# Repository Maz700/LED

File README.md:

# LED
My first project is the LED Chaser board. Since I am a complete beginner, my first project is a small and simple project just to learn the basics of PCB design and learn soldering. I am following the Blinky guide for this project. I am making the PCB in the shape of an my team's oar blade because I like rowing.

| Reference | Item              | Description                     | Quantity | Unit Price (USD) | Total (USD) | Link                                                                                                                           |
|----------|-------------------|---------------------------------|----------|------------------|-------------|--------------------------------------------------------------------------------------------------------------------------------|
| C1       | Capacitor         | CAP ALUM 1UF 20% 50V RADIAL TH  | 1        | $0.10            | $0.10       | https://www.digikey.com/en/products/detail/w%C3%BCrth-elektronik/860020672005/5727088                                          |
| C2       | Capacitor         | CER CAP 0.01UF 50V              | 1        | $0.24            | $0.24       | https://www.digikey.com/en/products/detail/kemet/C410C103Z5U5TA7200/12701821                                                   |
| D1-10    | LED               | LED COOL WHITE 5MM ROUND T/H    | 10       | $0.22            | $2.23       | https://www.digikey.com/en/products/detail/cree-led/C543A-WMN-CCCKK141/9959490                                                 |
| R1       | Resistor          | RES 1K OHM 1% 1/4W AXIAL        | 1        | $0.10            | $0.10       | https://www.digikey.com/en/products/detail/yageo/MFR-25FRF52-1K/14891                                                          |
| R2       | Resistor          | RES 470 OHM 1% 1/4W AXIAL       | 1        | $0.10            | $0.10       | https://www.digikey.com/en/products/detail/yageo/MFR-25FBF52-470R/9138172?s=N4IgTCBcDaILIDEBKBaMBWBAhB6woBYB2ABlQDkAREAXQF8g   |
| RV1      | Variable Resistor | TRIMMER 50K OHM 0.5W PC PIN TOP | 1        | $2.20            | $2.20       | https://www.digikey.com/en/products/detail/bourns-inc/3386P-1-503TLF/1232551?s=N4IgTCBcDaIMxwBwDYAKBaArABjgFQBkAxdAOQBEQBdAXyA |
| TP1      | Test Point        | PC TEST POINT SLOTTED           | 1        | $0.15            | $0.15       | https://www.digikey.com/en/products/detail/keystone-electronics/1035/315151                                                    |
| TP2      | Test Point        | PC TEST POINT SLOTTED           | 1        | $0.15            | $0.15       | https://www.digikey.com/en/products/detail/keystone-electronics/1035/315151                                                    |
| TP3      | Test Point        | PC TEST POINT SLOTTED           | 1        | $0.15            | $0.15       | https://www.digikey.com/en/products/detail/keystone-electronics/1035/315151                                                    |
| U1       | NE555PS           | IC OSC TIMER SINGLE 100KHZ 8SO  | 1        | $1.10            | $1.10       | https://www.digikey.com/en/products/detail/texas-instruments/NE555PS/9692573?s=N4IgTCBcDa4JwDYC0A5AogViwBQMqoBEQBdAXyA         |
| U2       | CD4017BE          | IC DECADE COUNTER 10BIT 16DIP   | 1        | $1.27            | $1.27       | https://www.digikey.com/en/products/detail/texas-instruments/CD4017BE/67253      
| PCB      | PCB               | PCB                             | 1        | $2               | $2          | https://cart.jlcpcb.com/quote                                                                                               |

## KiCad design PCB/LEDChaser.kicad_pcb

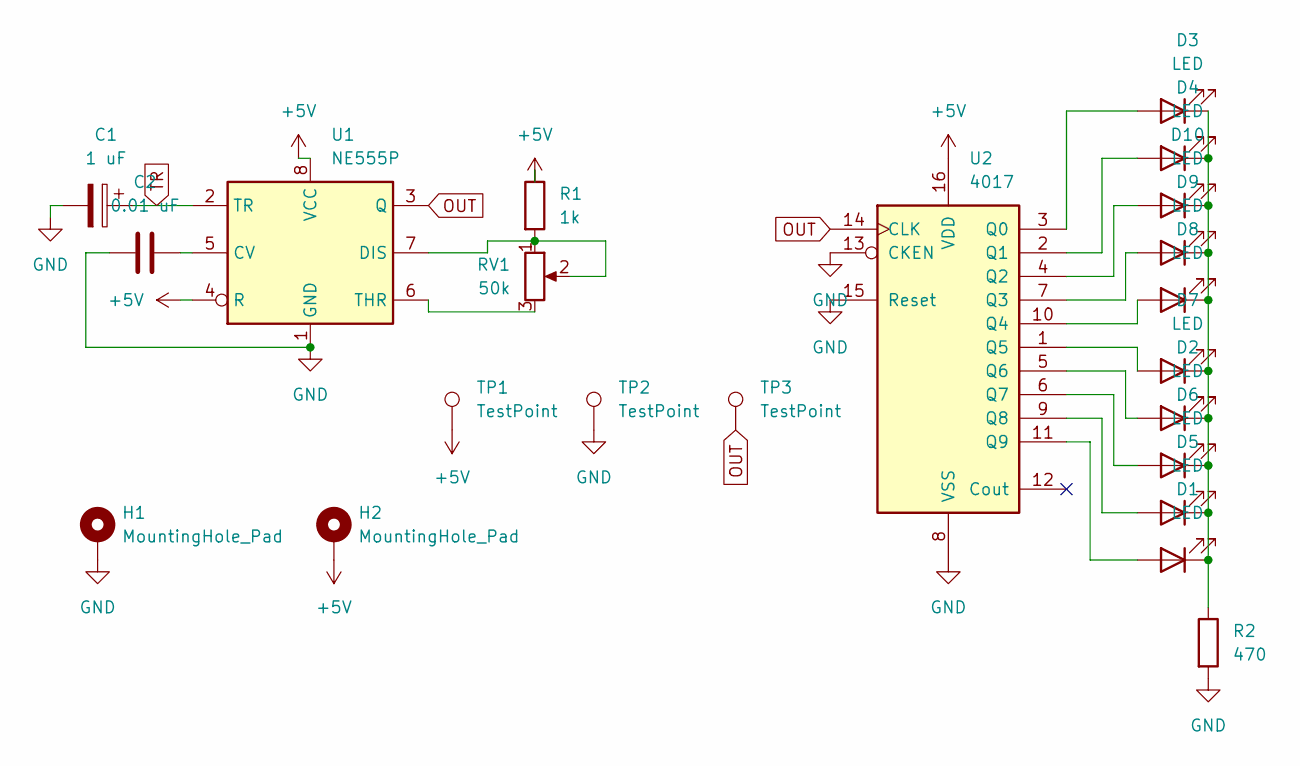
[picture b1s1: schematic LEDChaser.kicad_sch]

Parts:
C1: 1 uF; CP_Radial_D5.0mm_P2.00mm
C2: 0.01 uF; CP_Radial_D5.0mm_P2.00mm
D1, D2, D3, D4, D5, D6, D7, D8, D9, D10: LED; LED_D3.0mm
H1, H2: MountingHole_Pad; MountingHole_2.5mm_Pad
R1: 1k; R_Axial_DIN0207_L6.3mm_D2.5mm_P7.62mm_Horizontal
R2: 470; R_Axial_DIN0207_L6.3mm_D2.5mm_P7.62mm_Horizontal
RV1: 50k; Potentiometer_Bourns_3386P_Vertical
TP1, TP2, TP3: TestPoint; PinSocket_1x01_P2.54mm_Vertical
U1: NE555P; DIP-8_W7.62mm
U2: 4017; N16

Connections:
+5V: H2.1, R1.1, TP1.1, U1.4 (R), U1.8 (VCC), U2.16 (VDD)
GND: C1.2, C2.1, H1.1, R2.2, TP2.1, U1.1 (GND), U2.8 (VSS), U2.13 (CKEN), U2.15 (Reset)
unnamed: D1.2 (A), U2.11 (Q9)
unnamed: D1.1 (K), D2.1 (K), D3.1 (K), D4.1 (K), D5.1 (K), D6.1 (K), D7.1 (K), D8.1 (K), D9.1 (K), D10.1 (K), R2.1
unnamed: D2.2 (A), U2.5 (Q6)
unnamed: D3.2 (A), U2.3 (Q0)
unnamed: D4.2 (A), U2.2 (Q1)
unnamed: D5.2 (A), U2.9 (Q8)
unnamed: D6.2 (A), U2.6 (Q7)
unnamed: D7.2 (A), U2.1 (Q5)
unnamed: D8.2 (A), U2.10 (Q4)
unnamed: D9.2 (A), U2.7 (Q3)
unnamed: D10.2 (A), U2.4 (Q2)
unnamed: C2.2, U1.5 (CV)
unnamed: R1.2, RV1.1, RV1.2, U1.7 (DIS)
unnamed: RV1.3, U1.6 (THR)
OUT: TP3.1, U1.3 (Q), U2.14 (CLK)
TR: C1.1, U1.2 (TR)

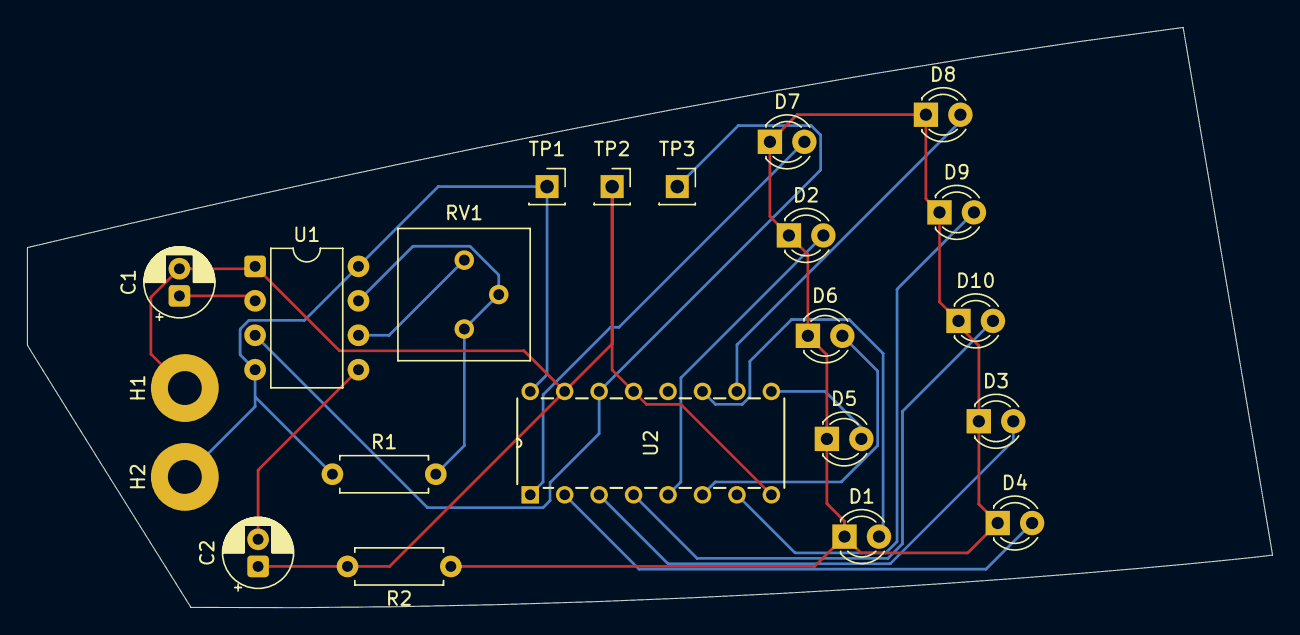
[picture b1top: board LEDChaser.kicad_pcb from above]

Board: 2 copper layers, 91.8 x 42.8 mm, 22 parts (0 on the bottom side), 18 nets.

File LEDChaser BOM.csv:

"Id";"Designator";"Footprint";"Quantity";"Designation";"Supplier and ref";
1;"D9,D4,D1,D3,D5,D10,D2,D6,D7,D8";"LED_D3.0mm";10;"LED";;;
2;"TP2,TP3,TP1";"PinSocket_1x01_P2.54mm_Vertical";3;"TestPoint";;;
3;"R1";"R_Axial_DIN0207_L6.3mm_D2.5mm_P7.62mm_Horizontal";1;"1k";;;
4;"C1";"CP_Radial_D5.0mm_P2.00mm";1;"1 uF";;;
5;"U1";"DIP-8_W7.62mm";1;"NE555P";;;
6;"RV1";"Potentiometer_Bourns_3386P_Vertical";1;"50k";;;
7;"C2";"CP_Radial_D5.0mm_P2.00mm";1;"0.01 uF";;;
8;"U2";"N16";1;"4017";;;
9;"R2";"R_Axial_DIN0207_L6.3mm_D2.5mm_P7.62mm_Horizontal";1;"470";;;

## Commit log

2025-12-27 Update README.md
    added BOM in table form
2025-12-27 Update README.md
    added schematic and pcb screenshots
2025-12-31 added PCB to BOM?
2025-12-31 pcb to BOM in readme
